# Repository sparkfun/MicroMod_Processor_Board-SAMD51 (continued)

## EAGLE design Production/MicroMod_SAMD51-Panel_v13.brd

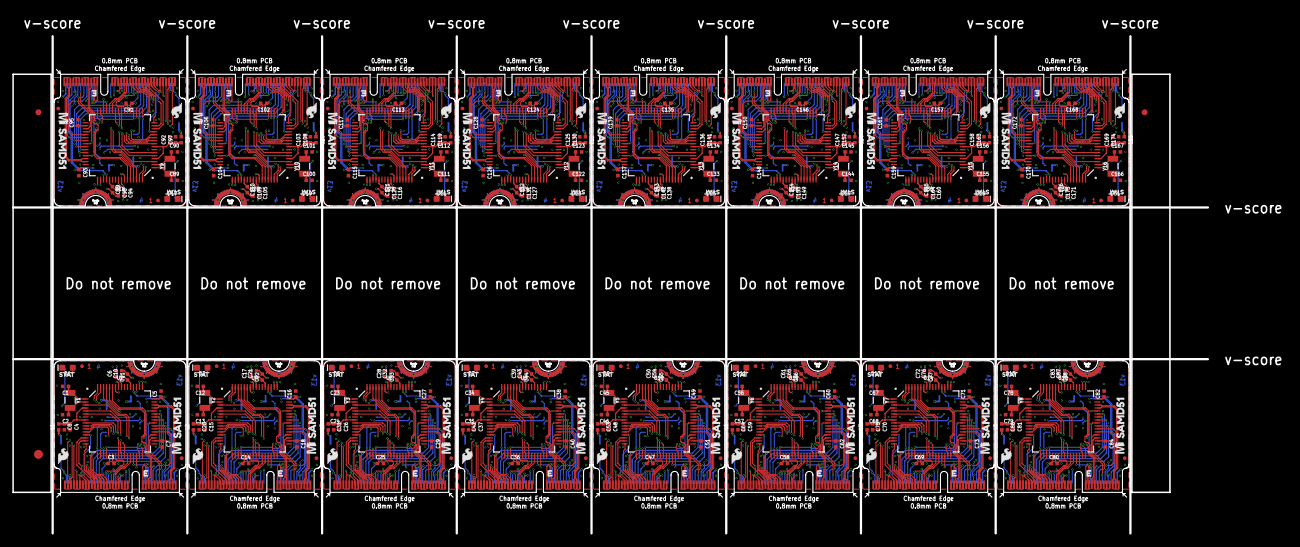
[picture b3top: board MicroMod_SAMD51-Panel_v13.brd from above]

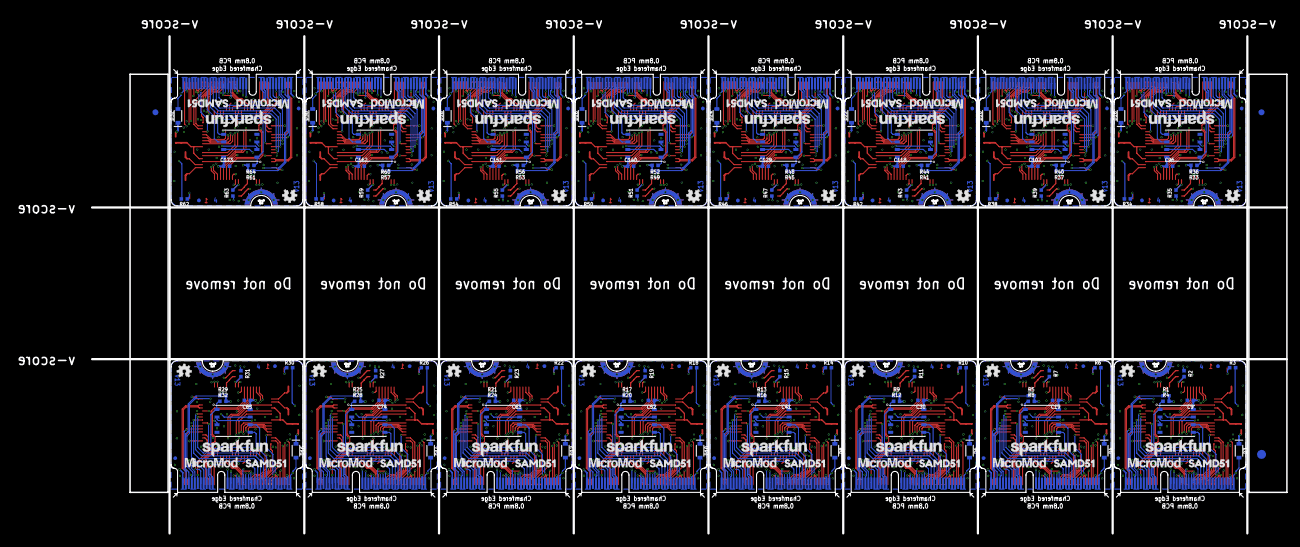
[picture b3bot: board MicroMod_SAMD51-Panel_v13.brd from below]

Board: 4 copper layers, 199.6 x 83.1 mm, 550 parts (211 on the bottom side), 912 nets.

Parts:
C1, C2, C12, C13, C23, C24, C34, C35, C45, C46, C56, C57, C67, C68, C78, C79, C89, C90, C100, C101, C111, C112, C122, C123, C133, C134, C144, C145, C155, C156, C166, C167: 15pF; 0402-TIGHT
C3, C5, C6, C7, C9, C10, C14, C16, C17, C18, C19, C21, C25, C27, C28, C29, C30, C32, C36, C38, C39, C40, C41, C43, C47, C49, C50, C51, C52, C54, C58, C60, C61, C62, C63, C65, C69, C71, C72, C73, C74, C76, C80, C82, C83, C84, C85, C87, C91, C93, C94, C95, C96, C98, C102, C104, C105, C106, C107, C109, C113, C115, C116, C117, C118, C120, C124, C126, C127, C128, C129, C131, C135, C137, C138, C139, C140, C142, C146, C148, C149, C150, C151, C153, C157, C159, C160, C161, C162, C164, C168, C170, C171, C172, C173, C175: 0.1uF; 0402-TIGHT
C4, C8, C15, C20, C26, C31, C37, C42, C48, C53, C59, C64, C70, C75, C81, C86, C92, C97, C103, C108, C114, C119, C125, C130, C136, C141, C147, C152, C158, C163, C169, C174: 10uF; 0402-TIGHT
C11, C22, C33, C44, C55, C66, C77, C88, C99, C110, C121, C132, C143, C154, C165, C176: 4.7uF; 0402-TIGHT
D1, D2, D5, D7, D9, D11, D13, D15, D17, D19, D21, D23, D25, D27, D29, D31: BLUE; LED-0603
D3, D4, D6, D8, D10, D12, D14, D16, D18, D20, D22, D24, D26, D28, D30, D32: 1A/23V/620mV; SOD-323
E$1, E$2, E$3, E$4: FIDUCIAL-1X2
E$5, E$6: FIDUCIAL-1.5X3
FD1, FD2, FD3, FD4, FD5, FD6, FD7, FD8, FD9, FD10, FD11, FD12, FD13, FD14, FD15, FD16, FD17, FD18, FD19, FD20, FD21, FD22, FD23, FD24, FD25, FD26, FD27, FD28, FD29, FD30, FD31, FD32, FD33, FD34, FD35, FD36, FD37, FD38, FD39, FD40, FD41, FD42, FD43, FD44, FD45, FD46, FD47, FD48, FD49, FD50, FD51, FD52, FD53, FD54, FD55, FD56, FD57, FD58, FD59, FD60, FD61, FD62, FD63, FD64: FIDUCIALUFIDUCIAL; FIDUCIAL-MICRO
J1, J2, J3, J4, J5, J6, J7, J8, J9, J10, J11, J12, J13, J14, J15, J16: MICROMOD-2222; M.2-CARD-E-22
L1, L2, L3, L4, L5, L6, L7, L8, L9, L10, L11, L12, L13, L14, L15, L16: 30Ω; 0402-TIGHT
LOGO1, LOGO2, LOGO4, LOGO7, LOGO9, LOGO11, LOGO13, LOGO15, LOGO17, LOGO19, LOGO21, LOGO23, LOGO25, LOGO27, LOGO29, LOGO31: OSHW-LOGOMINI; OSHW-LOGO-MINI
LOGO3, LOGO5, LOGO6, LOGO8, LOGO10, LOGO12, LOGO14, LOGO16, LOGO18, LOGO20, LOGO22, LOGO24, LOGO26, LOGO28, LOGO30, LOGO32: SFE_LOGO_NAME.1_INCH; SFE_LOGO_NAME_.1
R1, R5, R9, R13, R17, R21, R25, R29, R33, R37, R41, R45, R49, R53, R57, R61: 10k; 0402-TIGHT
R2, R3, R6, R7, R10, R11, R14, R15, R18, R19, R22, R23, R26, R27, R30, R31, R34, R35, R38, R39, R42, R43, R46, R47, R50, R51, R54, R55, R58, R59, R62, R63: 1k; 0402-TIGHT
R4, R8, R12, R16, R20, R24, R28, R32, R36, R40, R44, R48, R52, R56, R60, R64: 100k; 0402-TIGHT
U1, U3, U5, U7, U9, U11, U13, U15, U17, U19, U21, U23, U25, U27, U29, U31: W25QXX128MBIT-6X5-NO_CENTER; WSON-8-6X5-NO_CENTERPAD
U2, U4, U6, U8, U10, U12, U14, U16, U18, U20, U22, U24, U26, U28, U30, U32: ATSAMD51J20A-A; TQFP64
U$1, U$11, U$17, U$23, U$29, U$35, U$41, U$47, U$53, U$59, U$65, U$71, U$77, U$83, U$89, U$95: MICROMOD_MI_LOGO_.35
U$2, U$3, U$5, U$6, U$13, U$14, U$19, U$20, U$25, U$26, U$31, U$32, U$37, U$38, U$43, U$44, U$49, U$50, U$55, U$56, U$61, U$62, U$67, U$68, U$73, U$74, U$79, U$80, U$85, U$86, U$91, U$92: SAMD510
U$4, U$12, U$18, U$24, U$30, U$36, U$42, U$48, U$54, U$60, U$66, U$72, U$78, U$84, U$90, U$96: MICROMOD_LOGO_.35
U$7, U$9, U$15, U$21, U$27, U$33, U$39, U$45, U$51, U$57, U$63, U$69, U$75, U$81, U$87, U$93: SFE_LOGO_FLAME_.1
U$8, U$10, U$16, U$22, U$28, U$34, U$40, U$46, U$52, U$58, U$64, U$70, U$76, U$82, U$88, U$94: STAT0
Y1, Y2, Y3, Y4, Y5, Y6, Y7, Y8, Y9, Y10, Y11, Y12, Y13, Y14, Y15, Y16: 32.768kHz; CRYSTAL-SMD-3.2X1.5MM

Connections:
3.3V: C3.1, C5.1, C6.1, C7.1, C9.1, D3.C, J2.72, L1.1, R1.2, R2.2, R4.2, U1.8, U2.21, U2.34, U2.48, U2.56
3.3V1: C14.1, C16.1, C17.1, C18.1, C19.1, D4.C, J1.72, L2.1, R5.2, R7.2, R8.2, U3.8, U4.21, U4.34, U4.48, U4.56
3.3V2: C25.1, C27.1, C28.1, C29.1, C30.1, D6.C, J3.72, L3.1, R9.2, R11.2, R12.2, U5.8, U6.21, U6.34, U6.48, U6.56
3.3V3: C36.1, C38.1, C39.1, C40.1, C41.1, D8.C, J4.72, L4.1, R13.2, R15.2, R16.2, U7.8, U8.21, U8.34, U8.48, U8.56
3.3V4: C47.1, C49.1, C50.1, C51.1, C52.1, D10.C, J5.72, L5.1, R17.2, R19.2, R20.2, U9.8, U10.21, U10.34, U10.48, U10.56
3.3V5: C58.1, C60.1, C61.1, C62.1, C63.1, D12.C, J6.72, L6.1, R21.2, R23.2, R24.2, U11.8, U12.21, U12.34, U12.48, U12.56
3.3V6: C69.1, C71.1, C72.1, C73.1, C74.1, D14.C, J7.72, L7.1, R25.2, R27.2, R28.2, U13.8, U14.21, U14.34, U14.48, U14.56
3.3V7: C80.1, C82.1, C83.1, C84.1, C85.1, D16.C, J8.72, L8.1, R29.2, R31.2, R32.2, U15.8, U16.21, U16.34, U16.48, U16.56
3.3V8: C91.1, C93.1, C94.1, C95.1, C96.1, D18.C, J9.72, L9.1, R33.2, R35.2, R36.2, U17.8, U18.21, U18.34, U18.48, U18.56
3.3V9: C102.1, C104.1, C105.1, C106.1, C107.1, D20.C, J10.72, L10.1, R37.2, R39.2, R40.2, U19.8, U20.21, U20.34, U20.48, U20.56
3.3V10: C113.1, C115.1, C116.1, C117.1, C118.1, D22.C, J11.72, L11.1, R41.2, R43.2, R44.2, U21.8, U22.21, U22.34, U22.48, U22.56
3.3V11: C124.1, C126.1, C127.1, C128.1, C129.1, D24.C, J12.72, L12.1, R45.2, R47.2, R48.2, U23.8, U24.21, U24.34, U24.48, U24.56
3.3V12: C135.1, C137.1, C138.1, C139.1, C140.1, D26.C, J13.72, L13.1, R49.2, R51.2, R52.2, U25.8, U26.21, U26.34, U26.48, U26.56
3.3V13: C146.1, C148.1, C149.1, C150.1, C151.1, D28.C, J14.72, L14.1, R53.2, R55.2, R56.2, U27.8, U28.21, U28.34, U28.48, U28.56
3.3V14: C157.1, C159.1, C160.1, C161.1, C162.1, D30.C, J15.72, L15.1, R57.2, R59.2, R60.2, U29.8, U30.21, U30.34, U30.48, U30.56
3.3V15: C168.1, C170.1, C171.1, C172.1, C173.1, D32.C, J16.72, L16.1, R61.2, R63.2, R64.2, U31.8, U32.21, U32.34, U32.48, U32.56
3.3V_EN: J2.4, U2.38
3.3V_EN1: J1.4, U4.38
3.3V_EN2: J3.4, U6.38
3.3V_EN3: J4.4, U8.38
3.3V_EN4: J5.4, U10.38
3.3V_EN5: J6.4, U12.38
3.3V_EN6: J7.4, U14.38
3.3V_EN7: J8.4, U16.38
3.3V_EN8: J9.4, U18.38
3.3V_EN9: J10.4, U20.38
3.3V_EN10: J11.4, U22.38
3.3V_EN11: J12.4, U24.38
3.3V_EN12: J13.4, U26.38
3.3V_EN13: J14.4, U28.38
3.3V_EN14: J15.4, U30.38
3.3V_EN15: J16.4, U32.38
3.3V_IN: D3.A, J2.2, J2.74
3.3V_IN1: D4.A, J1.2, J1.74
3.3V_IN2: D6.A, J3.2, J3.74
3.3V_IN3: D8.A, J4.2, J4.74
3.3V_IN4: D10.A, J5.2, J5.74
3.3V_IN5: D12.A, J6.2, J6.74
3.3V_IN6: D14.A, J7.2, J7.74
3.3V_IN7: D16.A, J8.2, J8.74
3.3V_IN8: D18.A, J9.2, J9.74
3.3V_IN9: D20.A, J10.2, J10.74
3.3V_IN10: D22.A, J11.2, J11.74
3.3V_IN11: D24.A, J12.2, J12.74
3.3V_IN12: D26.A, J13.2, J13.74
3.3V_IN13: D28.A, J14.2, J14.74
3.3V_IN14: D30.A, J15.2, J15.74
3.3V_IN15: D32.A, J16.2, J16.74
!CS: J2.55, U2.16
!CS1: J1.55, U4.16
!CS1!: R4.1, U1.1, U2.20
!CS1!1: R8.1, U3.1, U4.20
!CS1!2: R12.1, U5.1, U6.20
!CS1!3: R16.1, U7.1, U8.20
!CS1!4: R20.1, U9.1, U10.20
!CS1!5: R24.1, U11.1, U12.20
!CS1!6: R28.1, U13.1, U14.20
!CS1!7: R32.1, U15.1, U16.20
!CS1!8: R36.1, U17.1, U18.20
!CS1!9: R40.1, U19.1, U20.20
!CS1!10: R44.1, U21.1, U22.20
!CS1!11: R48.1, U23.1, U24.20
!CS1!12: R52.1, U25.1, U26.20
!CS1!13: R56.1, U27.1, U28.20
!CS1!14: R60.1, U29.1, U30.20
!CS1!15: R64.1, U31.1, U32.20
!CS2: J3.55, U6.16
!CS3: J4.55, U8.16
!CS4: J5.55, U10.16
!CS5: J6.55, U12.16
!CS6: J7.55, U14.16
!CS7: J8.55, U16.16
!CS8: J9.55, U18.16
!CS9: J10.55, U20.16
!CS10: J11.55, U22.16
!CS11: J12.55, U24.16
!CS12: J13.55, U26.16
!CS13: J14.55, U28.16
!CS14: J15.55, U30.16
!CS15: J16.55, U32.16
!HOLD!: U1.7, U2.50
!HOLD!1: U3.7, U4.50
!HOLD!2: U5.7, U6.50
!HOLD!3: U7.7, U8.50
!HOLD!4: U9.7, U10.50
!HOLD!5: U11.7, U12.50
!HOLD!6: U13.7, U14.50
!HOLD!7: U15.7, U16.50
!HOLD!8: U17.7, U18.50
!HOLD!9: U19.7, U20.50
!HOLD!10: U21.7, U22.50
!HOLD!11: U23.7, U24.50
!HOLD!12: U25.7, U26.50
!HOLD!13: U27.7, U28.50
!HOLD!14: U29.7, U30.50
!HOLD!15: U31.7, U32.50
!RESET: J2.6, R1.1, U2.52
!RESET1: J1.6, R5.1, U4.52
!RESET2: J3.6, R9.1, U6.52
!RESET3: J4.6, R13.1, U8.52
!RESET4: J5.6, R17.1, U10.52
!RESET5: J6.6, R21.1, U12.52
!RESET6: J7.6, R25.1, U14.52
!RESET7: J8.6, R29.1, U16.52
!RESET8: J9.6, R33.1, U18.52
!RESET9: J10.6, R37.1, U20.52
!RESET10: J11.6, R41.1, U22.52
!RESET11: J12.6, R45.1, U24.52
!RESET12: J13.6, R49.1, U26.52
!RESET13: J14.6, R53.1, U28.52
!RESET14: J15.6, R57.1, U30.52
!RESET15: J16.6, R61.1, U32.52
!WP!: U1.3, U2.49
!WP!1: U3.3, U4.49
!WP!2: U5.3, U6.49
!WP!3: U7.3, U8.49
!WP!4: U9.3, U10.49
!WP!5: U11.3, U12.49
!WP!6: U13.3, U14.49
!WP!7: U15.3, U16.49
!WP!8: U17.3, U18.49
!WP!9: U19.3, U20.49
!WP!10: U21.3, U22.49
!WP!11: U23.3, U24.49
!WP!12: U25.3, U26.49
!WP!13: U27.3, U28.49
!WP!14: U29.3, U30.49
!WP!15: U31.3, U32.49
A0/DAC: J2.34, U2.3
A0/DAC1: J1.34, U4.3
A0/DAC2: J3.34, U6.3
A0/DAC3: J4.34, U8.3
A0/DAC4: J5.34, U10.3
A0/DAC5: J6.34, U12.3
A0/DAC6: J7.34, U14.3
A0/DAC7: J8.34, U16.3
A0/DAC8: J9.34, U18.3
A0/DAC9: J10.34, U20.3
A0/DAC10: J11.34, U22.3
A0/DAC11: J12.34, U24.3
A0/DAC12: J13.34, U26.3
A0/DAC13: J14.34, U28.3
A0/DAC14: J15.34, U30.3
A0/DAC15: J16.34, U32.3
A1: J2.38, U2.61
A2: J1.38, U4.61
A2/PWM0: J2.32, U2.62
A2/PWM1: J1.32, U4.62
A2/PWM2: J3.32, U6.62
A2/PWM3: J4.32, U8.62
A2/PWM4: J5.32, U10.62
A2/PWM5: J6.32, U12.62
A2/PWM6: J7.32, U14.62
A2/PWM7: J8.32, U16.62
A2/PWM8: J9.32, U18.62
A2/PWM9: J10.32, U20.62
A2/PWM10: J11.32, U22.62
A2/PWM11: J12.32, U24.62
A2/PWM12: J13.32, U26.62
A2/PWM13: J14.32, U28.62
A2/PWM14: J15.32, U30.62
A2/PWM15: J16.32, U32.62
A3: J1.49, U4.64
A3/PWM1: J2.47, U2.63
A3/PWM2: J1.47, U4.63
A3/PWM3: J3.47, U6.63
A3/PWM4: J4.47, U8.63
A3/PWM5: J5.47, U10.63
A3/PWM6: J6.47, U12.63
A3/PWM7: J7.47, U14.63
A3/PWM8: J8.47, U16.63
A3/PWM9: J9.47, U18.63
A3/PWM10: J10.47, U20.63
A3/PWM11: J11.47, U22.63
A3/PWM12: J12.47, U24.63
A3/PWM13: J13.47, U26.63
A3/PWM14: J14.47, U28.63
A3/PWM15: J15.47, U30.63
A3/PWM16: J16.47, U32.63
A4: J2.49, U2.64
A5: J3.38, U6.61
A6: J3.49, U6.64
A7: J4.38, U8.61
A8: J4.49, U8.64
A9: J5.38, U10.61
A10: J5.49, U10.64
A11: J6.38, U12.61
A12: J6.49, U12.64
A13: J7.38, U14.61
A14: J7.49, U14.64
A15: J8.38, U16.61
A16: J8.49, U16.64
A17: J9.38, U18.61
A18: J9.49, U18.64
A19: J10.38, U20.61
A20: J10.49, U20.64
A21: J11.38, U22.61
A22: J11.49, U22.64
A23: J12.38, U24.61
A24: J12.49, U24.64
A25: J13.38, U26.61
A26: J13.49, U26.64
A27: J14.38, U28.61
A28: J14.49, U28.64
A29: J15.38, U30.61
A30: J15.49, U30.64
A31: J16.38, U32.61
A32: J16.49, U32.64
CIPO: J2.61, U2.15
CIPO1: U1.2, U2.19
CIPO2: J1.61, U4.15
CIPO3: U3.2, U4.19
CIPO4: J3.61, U6.15
CIPO5: U5.2, U6.19
CIPO6: J4.61, U8.15
CIPO7: U7.2, U8.19
CIPO8: J5.61, U10.15
CIPO9: U9.2, U10.19
CIPO10: J6.61, U12.15
CIPO11: U11.2, U12.19
CIPO12: J7.61, U14.15
CIPO13: U13.2, U14.19
CIPO14: J8.61, U16.15
CIPO15: U15.2, U16.19
CIPO16: J9.61, U18.15
CIPO17: U17.2, U18.19
CIPO18: J10.61, U20.15
CIPO19: U19.2, U20.19
CIPO20: J11.61, U22.15
CIPO21: U21.2, U22.19
CIPO22: J12.61, U24.15
CIPO23: U23.2, U24.19
CIPO24: J13.61, U26.15
CIPO25: U25.2, U26.19
CIPO26: J14.61, U28.15
CIPO27: U27.2, U28.19
CIPO28: J15.61, U30.15
CIPO29: U29.2, U30.19
CIPO30: J16.61, U32.15
CIPO31: U31.2, U32.19
COPI: J2.59, U2.13
COPI1: U1.5, U2.18
COPI2: J1.59, U4.13
COPI3: U3.5, U4.18
COPI4: J3.59, U6.13
COPI5: U5.5, U6.18
COPI6: J4.59, U8.13
COPI7: U7.5, U8.18
COPI8: J5.59, U10.13
COPI9: U9.5, U10.18
COPI10: J6.59, U12.13
COPI11: U11.5, U12.18
COPI12: J7.59, U14.13
COPI13: U13.5, U14.18
COPI14: J8.59, U16.13
COPI15: U15.5, U16.18
COPI16: J9.59, U18.13
COPI17: U17.5, U18.18
COPI18: J10.59, U20.13
COPI19: U19.5, U20.18
COPI20: J11.59, U22.13
COPI21: U21.5, U22.18
COPI22: J12.59, U24.13
COPI23: U23.5, U24.18
COPI24: J13.59, U26.13
COPI25: U25.5, U26.18
COPI26: J14.59, U28.13
COPI27: U27.5, U28.18
COPI28: J15.59, U30.13
COPI29: U29.5, U30.18
COPI30: J16.59, U32.13
COPI31: U31.5, U32.18
D0: J2.10, U2.5
D1: J2.18, U2.6
D2: R6.2, U4.44
D2/G0: J2.40, U2.9
D2/G1: J1.40, U4.9
D2/G2: J3.40, U6.9
D2/G3: J4.40, U8.9
D2/G4: J5.40, U10.9
D2/G5: J6.40, U12.9
D2/G6: J7.40, U14.9
D2/G7: J8.40, U16.9
D2/G8: J9.40, U18.9
D2/G9: J10.40, U20.9
D2/G10: J11.40, U22.9
D2/G11: J12.40, U24.9
D2/G12: J13.40, U26.9
D2/G13: J14.40, U28.9
D2/G14: J15.40, U30.9
D2/G15: J16.40, U32.9
D3: J1.10, U4.5
D3/G1: J2.42, U2.10
D3/G2: J1.42, U4.10
D3/G3: J3.42, U6.10
D3/G4: J4.42, U8.10
D3/G5: J5.42, U10.10
D3/G6: J6.42, U12.10
D3/G7: J7.42, U14.10
D3/G8: J8.42, U16.10
D3/G9: J9.42, U18.10
D3/G10: J10.42, U20.10
D3/G11: J11.42, U22.10
D3/G12: J12.42, U24.10
D3/G13: J13.42, U26.10
D3/G14: J14.42, U28.10
D3/G15: J15.42, U30.10
D3/G16: J16.42, U32.10
D4: J1.18, U4.6
D4/G1: J1.44, U4.11
D4/G2: J2.44, U2.11
D4/G3: J3.44, U6.11
D4/G4: J4.44, U8.11
D4/G5: J5.44, U10.11
D4/G6: J6.44, U12.11
D4/G7: J7.44, U14.11
D4/G8: J8.44, U16.11
D4/G9: J9.44, U18.11
D4/G10: J10.44, U20.11
D4/G11: J11.44, U22.11
D4/G12: J12.44, U24.11
D4/G13: J13.44, U26.11
D4/G14: J14.44, U28.11
D4/G15: J15.44, U30.11
D4/G16: J16.44, U32.11
D5: J1.43, U4.27
D5/G1: J1.46, U4.12
D5/G2: J3.46, U6.12
D5/G3: J2.46, U2.12
D5/G4: J4.46, U8.12
D5/G5: J5.46, U10.12
D5/G6: J6.46, U12.12
D5/G7: J7.46, U14.12
D5/G8: J8.46, U16.12
D5/G9: J9.46, U18.12
D5/G10: J10.46, U20.12
D5/G11: J11.46, U22.12
D5/G12: J12.46, U24.12
D5/G13: J13.46, U26.12
D5/G14: J14.46, U28.12
D5/G15: J15.46, U30.12
D5/G16: J16.46, U32.12
D6: J1.41, U4.28
D6/G1: J1.48, U4.23
D6/G2: J3.48, U6.23
D6/G3: J4.48, U8.23
D6/G4: J2.48, U2.23
D6/G5: J5.48, U10.23
D6/G6: J6.48, U12.23
D6/G7: J7.48, U14.23
D6/G8: J8.48, U16.23
D6/G9: J9.48, U18.23
D6/G10: J10.48, U20.23
D6/G11: J11.48, U22.23
D6/G12: J12.48, U24.23
D6/G13: J13.48, U26.23
D6/G14: J14.48, U28.23
D6/G15: J15.48, U30.23
D6/G16: J16.48, U32.23
D7: J1.67, U4.31
D7/G1: J1.73, U4.24
D7/G2: J3.73, U6.24
D7/G3: J4.73, U8.24
D7/G4: J5.73, U10.24
D7/G5: J2.73, U2.24
D7/G6: J6.73, U12.24
D7/G7: J7.73, U14.24
D7/G8: J8.73, U16.24
D7/G9: J9.73, U18.24
D7/G10: J10.73, U20.24
D7/G11: J11.73, U22.24
D7/G12: J12.73, U24.24
D7/G13: J13.73, U26.24
D7/G14: J14.73, U28.24
D7/G15: J15.73, U30.24
D7/G16: J16.73, U32.24
D8: J1.65, U4.32
D8/G1: J1.71, U4.25
D8/G2: J3.71, U6.25
D8/G3: J4.71, U8.25
D8/G4: J5.71, U10.25
D8/G5: J6.71, U12.25
D8/G6: J2.71, U2.25
D8/G7: J7.71, U14.25
D8/G8: J8.71, U16.25
D8/G9: J9.71, U18.25
D8/G10: J10.71, U20.25
D8/G11: J11.71, U22.25
D8/G12: J12.71, U24.25
D8/G13: J13.71, U26.25
D8/G14: J14.71, U28.25
D8/G15: J15.71, U30.25
D8/G16: J16.71, U32.25
D9: R10.2, U6.44
D9/G1: J1.69, U4.26
D9/G2: J3.69, U6.26
D9/G3: J4.69, U8.26
D9/G4: J5.69, U10.26
D9/G5: J6.69, U12.26
D9/G6: J7.69, U14.26
D9/G7: J2.69, U2.26
D9/G8: J8.69, U16.26
D9/G9: J9.69, U18.26
D9/G10: J10.69, U20.26
D9/G11: J11.69, U22.26
D9/G12: J12.69, U24.26
D9/G13: J13.69, U26.26
D9/G14: J14.69, U28.26
D9/G15: J15.69, U30.26
D9/G16: J16.69, U32.26
D10: J2.67, U2.31
D11: J2.65, U2.32
D12: J3.10, U6.5
D13: R3.2, U2.44
D14: J3.18, U6.6
D15: J3.43, U6.27
D16: J3.41, U6.28
D17: J3.67, U6.31
D18: J3.65, U6.32
D19: R14.2, U8.44
D20: J4.10, U8.5
D21: J4.18, U8.6
D22: J4.43, U8.27
D23: J4.41, U8.28
D24: J4.67, U8.31
D25: J4.65, U8.32
D26: R18.2, U10.44
D27: J5.10, U10.5
D28: J5.18, U10.6
D29: J5.43, U10.27
D30: J5.41, U10.28
D31: J5.67, U10.31
D32: J5.65, U10.32
D33: R22.2, U12.44
D34: J6.10, U12.5
D35: J6.18, U12.6
D36: J6.43, U12.27
D37: J6.41, U12.28
D38: J2.43, U2.27
D39: J2.41, U2.28
D40: J6.67, U12.31
D41: J6.65, U12.32
D42: R26.2, U14.44
D43: J7.10, U14.5
D44: J7.18, U14.6
D45: J7.43, U14.27
D46: J7.41, U14.28
D47: J7.67, U14.31
D48: J7.65, U14.32
D49: R30.2, U16.44
D50: J8.10, U16.5
D51: J8.18, U16.6
D52: J8.43, U16.27
D53: J8.41, U16.28
D54: J8.67, U16.31
D55: J8.65, U16.32
D56: R34.2, U18.44
D57: J9.10, U18.5
D58: J9.18, U18.6
D59: J9.43, U18.27
D60: J9.41, U18.28
D61: J9.67, U18.31
D62: J9.65, U18.32
D63: R38.2, U20.44
D64: J10.10, U20.5
D65: J10.18, U20.6
D66: J10.43, U20.27
D67: J10.41, U20.28
D68: J10.67, U20.31
D69: J10.65, U20.32
D70: R42.2, U22.44
D71: J11.10, U22.5
D72: J11.18, U22.6
D73: J11.43, U22.27
D74: J11.41, U22.28
D75: J11.67, U22.31
D76: J11.65, U22.32
D77: R46.2, U24.44
D78: J12.10, U24.5
D79: J12.18, U24.6
D80: J12.43, U24.27
D81: J12.41, U24.28
D82: J12.67, U24.31
D83: J12.65, U24.32
D84: R50.2, U26.44
D85: J13.10, U26.5
D86: J13.18, U26.6
D87: J13.43, U26.27
D88: J13.41, U26.28
D89: J13.67, U26.31
D90: J13.65, U26.32
D91: R54.2, U28.44
D92: J14.10, U28.5
D93: J14.18, U28.6
D94: J14.43, U28.27
D95: J14.41, U28.28
D96: J14.67, U28.31
D97: J14.65, U28.32
D98: R58.2, U30.44
D99: J15.10, U30.5
D100: J15.18, U30.6
D101: J15.43, U30.27
D102: J15.41, U30.28
D103: J15.67, U30.31
D104: J15.65, U30.32
D105: R62.2, U32.44
D106: J16.10, U32.5
D107: J16.18, U32.6
D108: J16.43, U32.27
D109: J16.41, U32.28
D110: J16.67, U32.31
D111: J16.65, U32.32
D+/USBHOST_D+: J2.3, U2.46
D+/USBHOST_D+1: J1.3, U4.46
D+/USBHOST_D+2: J3.3, U6.46
D+/USBHOST_D+3: J4.3, U8.46
D+/USBHOST_D+4: J5.3, U10.46
D+/USBHOST_D+5: J6.3, U12.46
D+/USBHOST_D+6: J7.3, U14.46
D+/USBHOST_D+7: J8.3, U16.46
D+/USBHOST_D+8: J9.3, U18.46
D+/USBHOST_D+9: J10.3, U20.46
D+/USBHOST_D+10: J11.3, U22.46
D+/USBHOST_D+11: J12.3, U24.46
D+/USBHOST_D+12: J13.3, U26.46
D+/USBHOST_D+13: J14.3, U28.46
D+/USBHOST_D+14: J15.3, U30.46
D+/USBHOST_D+15: J16.3, U32.46
D-/USBHOST_D-: J2.5, U2.45
D-/USBHOST_D-1: J1.5, U4.45
D-/USBHOST_D-2: J3.5, U6.45
D-/USBHOST_D-3: J4.5, U8.45
D-/USBHOST_D-4: J5.5, U10.45
D-/USBHOST_D-5: J6.5, U12.45
D-/USBHOST_D-6: J7.5, U14.45
D-/USBHOST_D-7: J8.5, U16.45
D-/USBHOST_D-8: J9.5, U18.45
D-/USBHOST_D-9: J10.5, U20.45
D-/USBHOST_D-10: J11.5, U22.45
D-/USBHOST_D-11: J12.5, U24.45
D-/USBHOST_D-12: J13.5, U26.45
D-/USBHOST_D-13: J14.5, U28.45
D-/USBHOST_D-14: J15.5, U30.45
D-/USBHOST_D-15: J16.5, U32.45
GND: C1.2, C2.2, C3.2, C4.2, C5.2, C6.2, C7.2, C8.2, C9.2, C10.2, C11.2, D1.C, J2.1, J2.7, J2.33, J2.36, J2.39, J2.45, J2.75, J2.GND1, J2.GND2, J2.GND3, U1.4, U2.7, U2.22, U2.33, U2.47, U2.54
GND1: C12.2, C13.2, C14.2, C15.2, C16.2, C17.2, C18.2, C19.2, C20.2, C21.2, C22.2, D2.C, J1.1, J1.7, J1.33, J1.36, J1.39, J1.45, J1.75, J1.GND1, J1.GND2, J1.GND3, U3.4, U4.7, U4.22, U4.33, U4.47, U4.54
GND2: C23.2, C24.2, C25.2, C26.2, C27.2, C28.2, C29.2, C30.2, C31.2, C32.2, C33.2, D5.C, J3.1, J3.7, J3.33, J3.36, J3.39, J3.45, J3.75, J3.GND1, J3.GND2, J3.GND3, U5.4, U6.7, U6.22, U6.33, U6.47, U6.54
GND3: C34.2, C35.2, C36.2, C37.2, C38.2, C39.2, C40.2, C41.2, C42.2, C43.2, C44.2, D7.C, J4.1, J4.7, J4.33, J4.36, J4.39, J4.45, J4.75, J4.GND1, J4.GND2, J4.GND3, U7.4, U8.7, U8.22, U8.33, U8.47, U8.54
GND4: C45.2, C46.2, C47.2, C48.2, C49.2, C50.2, C51.2, C52.2, C53.2, C54.2, C55.2, D9.C, J5.1, J5.7, J5.33, J5.36, J5.39, J5.45, J5.75, J5.GND1, J5.GND2, J5.GND3, U9.4, U10.7, U10.22, U10.33, U10.47, U10.54
GND5: C56.2, C57.2, C58.2, C59.2, C60.2, C61.2, C62.2, C63.2, C64.2, C65.2, C66.2, D11.C, J6.1, J6.7, J6.33, J6.36, J6.39, J6.45, J6.75, J6.GND1, J6.GND2, J6.GND3, U11.4, U12.7, U12.22, U12.33, U12.47, U12.54
GND6: C67.2, C68.2, C69.2, C70.2, C71.2, C72.2, C73.2, C74.2, C75.2, C76.2, C77.2, D13.C, J7.1, J7.7, J7.33, J7.36, J7.39, J7.45, J7.75, J7.GND1, J7.GND2, J7.GND3, U13.4, U14.7, U14.22, U14.33, U14.47, U14.54
GND7: C78.2, C79.2, C80.2, C81.2, C82.2, C83.2, C84.2, C85.2, C86.2, C87.2, C88.2, D15.C, J8.1, J8.7, J8.33, J8.36, J8.39, J8.45, J8.75, J8.GND1, J8.GND2, J8.GND3, U15.4, U16.7, U16.22, U16.33, U16.47, U16.54
GND8: C89.2, C90.2, C91.2, C92.2, C93.2, C94.2, C95.2, C96.2, C97.2, C98.2, C99.2, D17.C, J9.1, J9.7, J9.33, J9.36, J9.39, J9.45, J9.75, J9.GND1, J9.GND2, J9.GND3, U17.4, U18.7, U18.22, U18.33, U18.47, U18.54
GND9: C100.2, C101.2, C102.2, C103.2, C104.2, C105.2, C106.2, C107.2, C108.2, C109.2, C110.2, D19.C, J10.1, J10.7, J10.33, J10.36, J10.39, J10.45, J10.75, J10.GND1, J10.GND2, J10.GND3, U19.4, U20.7, U20.22, U20.33, U20.47, U20.54
GND10: C111.2, C112.2, C113.2, C114.2, C115.2, C116.2, C117.2, C118.2, C119.2, C120.2, C121.2, D21.C, J11.1, J11.7, J11.33, J11.36, J11.39, J11.45, J11.75, J11.GND1, J11.GND2, J11.GND3, U21.4, U22.7, U22.22, U22.33, U22.47, U22.54
GND11: C122.2, C123.2, C124.2, C125.2, C126.2, C127.2, C128.2, C129.2, C130.2, C131.2, C132.2, D23.C, J12.1, J12.7, J12.33, J12.36, J12.39, J12.45, J12.75, J12.GND1, J12.GND2, J12.GND3, U23.4, U24.7, U24.22, U24.33, U24.47, U24.54
GND12: C133.2, C134.2, C135.2, C136.2, C137.2, C138.2, C139.2, C140.2, C141.2, C142.2, C143.2, D25.C, J13.1, J13.7, J13.33, J13.36, J13.39, J13.45, J13.75, J13.GND1, J13.GND2, J13.GND3, U25.4, U26.7, U26.22, U26.33, U26.47, U26.54
GND13: C144.2, C145.2, C146.2, C147.2, C148.2, C149.2, C150.2, C151.2, C152.2, C153.2, C154.2, D27.C, J14.1, J14.7, J14.33, J14.36, J14.39, J14.45, J14.75, J14.GND1, J14.GND2, J14.GND3, U27.4, U28.7, U28.22, U28.33, U28.47, U28.54
GND14: C155.2, C156.2, C157.2, C158.2, C159.2, C160.2, C161.2, C162.2, C163.2, C164.2, C165.2, D29.C, J15.1, J15.7, J15.33, J15.36, J15.39, J15.45, J15.75, J15.GND1, J15.GND2, J15.GND3, U29.4, U30.7, U30.22, U30.33, U30.47, U30.54
GND15: C166.2, C167.2, C168.2, C169.2, C170.2, C171.2, C172.2, C173.2, C174.2, C175.2, C176.2, D31.C, J16.1, J16.7, J16.33, J16.36, J16.39, J16.45, J16.75, J16.GND1, J16.GND2, J16.GND3, U31.4, U32.7, U32.22, U32.33, U32.47, U32.54
HOST_ENABLE: J2.8, U2.51
HOST_ENABLE1: J1.8, U4.51
HOST_ENABLE2: J3.8, U6.51
HOST_ENABLE3: J4.8, U8.51
HOST_ENABLE4: J5.8, U10.51
HOST_ENABLE5: J6.8, U12.51
HOST_ENABLE6: J7.8, U14.51
HOST_ENABLE7: J8.8, U16.51
HOST_ENABLE8: J9.8, U18.51
HOST_ENABLE9: J10.8, U20.51
HOST_ENABLE10: J11.8, U22.51
HOST_ENABLE11: J12.8, U24.51
HOST_ENABLE12: J13.8, U26.51
HOST_ENABLE13: J14.8, U28.51
HOST_ENABLE14: J15.8, U30.51
HOST_ENABLE15: J16.8, U32.51
I2C_!INT!: J2.16, U2.37
I2C_!INT!1: J1.16, U4.37
I2C_!INT!2: J3.16, U6.37
I2C_!INT!3: J4.16, U8.37
I2C_!INT!4: J5.16, U10.37
I2C_!INT!5: J6.16, U12.37
I2C_!INT!6: J7.16, U14.37
I2C_!INT!7: J8.16, U16.37
I2C_!INT!8: J9.16, U18.37
I2C_!INT!9: J10.16, U20.37
I2C_!INT!10: J11.16, U22.37
I2C_!INT!11: J12.16, U24.37
I2C_!INT!12: J13.16, U26.37
I2C_!INT!13: J14.16, U28.37
I2C_!INT!14: J15.16, U30.37
I2C_!INT!15: J16.16, U32.37
I2S_CLK: J2.50, U2.39
I2S_CLK1: J1.50, U4.39
I2S_CLK2: J3.50, U6.39
I2S_CLK3: J4.50, U8.39
I2S_CLK4: J5.50, U10.39
I2S_CLK5: J6.50, U12.39
I2S_CLK6: J7.50, U14.39
I2S_CLK7: J8.50, U16.39
I2S_CLK8: J9.50, U18.39
I2S_CLK9: J10.50, U20.39
I2S_CLK10: J11.50, U22.39
I2S_CLK11: J12.50, U24.39
I2S_CLK12: J13.50, U26.39
I2S_CLK13: J14.50, U28.39
I2S_CLK14: J15.50, U30.39
I2S_CLK15: J16.50, U32.39
I2S_FS: J2.52, U2.41
I2S_FS1: J1.52, U4.41
I2S_FS2: J3.52, U6.41
I2S_FS3: J4.52, U8.41
I2S_FS4: J5.52, U10.41
I2S_FS5: J6.52, U12.41
I2S_FS6: J7.52, U14.41
I2S_FS7: J8.52, U16.41
I2S_FS8: J9.52, U18.41
I2S_FS9: J10.52, U20.41
I2S_FS10: J11.52, U22.41
I2S_FS11: J12.52, U24.41
I2S_FS12: J13.52, U26.41
I2S_FS13: J14.52, U28.41
I2S_FS14: J15.52, U30.41
I2S_FS15: J16.52, U32.41
I2S_MCLK: J2.58, U2.40
I2S_MCLK1: J1.58, U4.40
I2S_MCLK2: J3.58, U6.40
I2S_MCLK3: J4.58, U8.40
I2S_MCLK4: J5.58, U10.40
I2S_MCLK5: J6.58, U12.40
I2S_MCLK6: J7.58, U14.40
I2S_MCLK7: J8.58, U16.40
I2S_MCLK8: J9.58, U18.40
I2S_MCLK9: J10.58, U20.40
I2S_MCLK10: J11.58, U22.40
I2S_MCLK11: J12.58, U24.40
I2S_MCLK12: J13.58, U26.40
I2S_MCLK13: J14.58, U28.40
I2S_MCLK14: J15.58, U30.40
I2S_MCLK15: J16.58, U32.40
I2S_SDI: J2.54, U2.43
I2S_SDI1: J1.54, U4.43
I2S_SDI2: J3.54, U6.43
I2S_SDI3: J4.54, U8.43
I2S_SDI4: J5.54, U10.43
I2S_SDI5: J6.54, U12.43
I2S_SDI6: J7.54, U14.43
I2S_SDI7: J8.54, U16.43
I2S_SDI8: J9.54, U18.43
I2S_SDI9: J10.54, U20.43
I2S_SDI10: J11.54, U22.43
I2S_SDI11: J12.54, U24.43
I2S_SDI12: J13.54, U26.43
I2S_SDI13: J14.54, U28.43
I2S_SDI14: J15.54, U30.43
I2S_SDI15: J16.54, U32.43
I2S_SDO: J2.56, U2.42
I2S_SDO1: J1.56, U4.42
I2S_SDO2: J3.56, U6.42
I2S_SDO3: J4.56, U8.42
I2S_SDO4: J5.56, U10.42
I2S_SDO5: J6.56, U12.42
I2S_SDO6: J7.56, U14.42
I2S_SDO7: J8.56, U16.42
I2S_SDO8: J9.56, U18.42
I2S_SDO9: J10.56, U20.42
I2S_SDO10: J11.56, U22.42
I2S_SDO11: J12.56, U24.42
I2S_SDO12: J13.56, U26.42
I2S_SDO13: J14.56, U28.42
I2S_SDO14: J15.56, U30.42
I2S_SDO15: J16.56, U32.42
unnamed: D1.A, R3.1
unnamed: D2.A, R6.1
unnamed: D5.A, R10.1
unnamed: D7.A, R14.1
unnamed: D9.A, R18.1
unnamed: D11.A, R22.1
unnamed: D13.A, R26.1
unnamed: D15.A, R30.1
unnamed: D17.A, R34.1
unnamed: D19.A, R38.1
unnamed: D21.A, R42.1
unnamed: D23.A, R46.1
unnamed: D25.A, R50.1
unnamed: D27.A, R54.1
unnamed: D29.A, R58.1
unnamed: D31.A, R62.1
RXI: J2.19, U2.59
RXI1: J1.19, U4.59
RXI2: J3.19, U6.59
RXI3: J4.19, U8.59
RXI4: J5.19, U10.59
RXI5: J6.19, U12.59
RXI6: J7.19, U14.59
RXI7: J8.19, U16.59
RXI8: J9.19, U18.59
RXI9: J10.19, U20.59
RXI10: J11.19, U22.59
RXI11: J12.19, U24.59
RXI12: J13.19, U26.59
RXI13: J14.19, U28.59
RXI14: J15.19, U30.59
RXI15: J16.19, U32.59
SCK: J2.57, U2.14
SCK1: U1.6, U2.17
SCK2: J1.57, U4.14
SCK3: U3.6, U4.17
SCK4: J3.57, U6.14
SCK5: U5.6, U6.17
SCK6: J4.57, U8.14
SCK7: U7.6, U8.17
SCK8: J5.57, U10.14
SCK9: U9.6, U10.17
SCK10: J6.57, U12.14
SCK11: U11.6, U12.17
SCK12: J7.57, U14.14
SCK13: U13.6, U14.17
SCK14: J8.57, U16.14
SCK15: U15.6, U16.17
SCK16: J9.57, U18.14
SCK17: U17.6, U18.17
SCK18: J10.57, U20.14
SCK19: U19.6, U20.17
SCK20: J11.57, U22.14
SCK21: U21.6, U22.17
SCK22: J12.57, U24.14
SCK23: U23.6, U24.17
SCK24: J13.57, U26.14
SCK25: U25.6, U26.17
SCK26: J14.57, U28.14
SCK27: U27.6, U28.17
SCK28: J15.57, U30.14
SCK29: U29.6, U30.17
SCK30: J16.57, U32.14
SCK31: U31.6, U32.17
SCL: J2.14, U2.35
SCL1: J1.14, U4.35
SCL1/TX1: J1.22, J1.53, U4.29
SCL1/TX2: J2.22, J2.53, U2.29
SCL1/TX3: J3.22, J3.53, U6.29
SCL1/TX4: J4.22, J4.53, U8.29
SCL1/TX5: J5.22, J5.53, U10.29
SCL1/TX6: J6.22, J6.53, U12.29
SCL1/TX7: J7.22, J7.53, U14.29
SCL1/TX8: J8.22, J8.53, U16.29
SCL1/TX9: J9.22, J9.53, U18.29
SCL1/TX10: J10.22, J10.53, U20.29
SCL1/TX11: J11.22, J11.53, U22.29
SCL1/TX12: J12.22, J12.53, U24.29
SCL1/TX13: J13.22, J13.53, U26.29
SCL1/TX14: J14.22, J14.53, U28.29
SCL1/TX15: J15.22, J15.53, U30.29
SCL1/TX16: J16.22, J16.53, U32.29
SCL2: J3.14, U6.35
SCL3: J4.14, U8.35
SCL4: J5.14, U10.35
SCL5: J6.14, U12.35
SCL6: J7.14, U14.35
SCL7: J8.14, U16.35
SCL8: J9.14, U18.35
SCL9: J10.14, U20.35
SCL10: J11.14, U22.35
SCL11: J12.14, U24.35
SCL12: J13.14, U26.35
SCL13: J14.14, U28.35
SCL14: J15.14, U30.35
SCL15: J16.14, U32.35
SDA: J2.12, U2.36
SDA1: J1.12, U4.36
SDA1/RX1: J1.20, J1.51, U4.30
SDA1/RX2: J2.20, J2.51, U2.30
SDA1/RX3: J3.20, J3.51, U6.30
SDA1/RX4: J4.20, J4.51, U8.30
SDA1/RX5: J5.20, J5.51, U10.30
SDA1/RX6: J6.20, J6.51, U12.30
SDA1/RX7: J7.20, J7.51, U14.30
SDA1/RX8: J8.20, J8.51, U16.30
SDA1/RX9: J9.20, J9.51, U18.30
SDA1/RX10: J10.20, J10.51, U20.30
SDA1/RX11: J11.20, J11.51, U22.30
SDA1/RX12: J12.20, J12.51, U24.30
SDA1/RX13: J13.20, J13.51, U26.30
SDA1/RX14: J14.20, J14.51, U28.30
SDA1/RX15: J15.20, J15.51, U30.30
SDA1/RX16: J16.20, J16.51, U32.30
SDA2: J3.12, U6.36
SDA3: J4.12, U8.36
SDA4: J5.12, U10.36
SDA5: J6.12, U12.36
SDA6: J7.12, U14.36
SDA7: J8.12, U16.36
SDA8: J9.12, U18.36
SDA9: J10.12, U20.36
SDA10: J11.12, U22.36
SDA11: J12.12, U24.36
SDA12: J13.12, U26.36
SDA13: J14.12, U28.36
SDA14: J15.12, U30.36
SDA15: J16.12, U32.36
SWDCK: J2.21, R2.1, U2.57
SWDCK1: J1.21, R7.1, U4.57
SWDCK2: J3.21, R11.1, U6.57
SWDCK3: J4.21, R15.1, U8.57
SWDCK4: J5.21, R19.1, U10.57
SWDCK5: J6.21, R23.1, U12.57
SWDCK6: J7.21, R27.1, U14.57
SWDCK7: J8.21, R31.1, U16.57
SWDCK8: J9.21, R35.1, U18.57
SWDCK9: J10.21, R39.1, U20.57
SWDCK10: J11.21, R43.1, U22.57
SWDCK11: J12.21, R47.1, U24.57
SWDCK12: J13.21, R51.1, U26.57
SWDCK13: J14.21, R55.1, U28.57
SWDCK14: J15.21, R59.1, U30.57
SWDCK15: J16.21, R63.1, U32.57
SWDIO: J2.23, U2.58
SWDIO1: J1.23, U4.58
SWDIO2: J3.23, U6.58
SWDIO3: J4.23, U8.58
SWDIO4: J5.23, U10.58
SWDIO5: J6.23, U12.58
SWDIO6: J7.23, U14.58
SWDIO7: J8.23, U16.58
SWDIO8: J9.23, U18.58
SWDIO9: J10.23, U20.58
SWDIO10: J11.23, U22.58
SWDIO11: J12.23, U24.58
SWDIO12: J13.23, U26.58
SWDIO13: J14.23, U28.58
SWDIO14: J15.23, U30.58
SWDIO15: J16.23, U32.58
TXO: J2.17, U2.60
TXO1: J1.17, U4.60
TXO2: J3.17, U6.60
TXO3: J4.17, U8.60
TXO4: J5.17, U10.60
TXO5: J6.17, U12.60
TXO6: J7.17, U14.60
TXO7: J8.17, U16.60
TXO8: J9.17, U18.60
TXO9: J10.17, U20.60
TXO10: J11.17, U22.60
TXO11: J12.17, U24.60
TXO12: J13.17, U26.60
TXO13: J14.17, U28.60
TXO14: J15.17, U30.60
TXO15: J16.17, U32.60
VCC: C10.1, C11.1, U2.53
VCC1: C21.1, C22.1, U4.53
VCC2: C32.1, C33.1, U6.53
VCC3: C43.1, C44.1, U8.53
VCC4: C54.1, C55.1, U10.53
VCC5: C65.1, C66.1, U12.53
VCC6: C76.1, C77.1, U14.53
VCC7: C87.1, C88.1, U16.53
VCC8: C98.1, C99.1, U18.53
VCC9: C109.1, C110.1, U20.53
VCC10: C120.1, C121.1, U22.53
VCC11: C131.1, C132.1, U24.53
VCC12: C142.1, C143.1, U26.53
VCC13: C153.1, C154.1, U28.53
VCC14: C164.1, C165.1, U30.53
VCC15: C175.1, C176.1, U32.53
VDDA: C4.1, C8.1, L1.2, U2.4, U2.8
VDDA1: C15.1, C20.1, L2.2, U4.4, U4.8
VDDA2: C26.1, C31.1, L3.2, U6.4, U6.8
VDDA3: C37.1, C42.1, L4.2, U8.4, U8.8
VDDA4: C48.1, C53.1, L5.2, U10.4, U10.8
VDDA5: C59.1, C64.1, L6.2, U12.4, U12.8
VDDA6: C70.1, C75.1, L7.2, U14.4, U14.8
VDDA7: C81.1, C86.1, L8.2, U16.4, U16.8
VDDA8: C92.1, C97.1, L9.2, U18.4, U18.8
VDDA9: C103.1, C108.1, L10.2, U20.4, U20.8
VDDA10: C114.1, C119.1, L11.2, U22.4, U22.8
VDDA11: C125.1, C130.1, L12.2, U24.4, U24.8
VDDA12: C136.1, C141.1, L13.2, U26.4, U26.8
VDDA13: C147.1, C152.1, L14.2, U28.4, U28.8
VDDA14: C158.1, C163.1, L15.2, U30.4, U30.8
VDDA15: C169.1, C174.1, L16.2, U32.4, U32.8
XIN1: C12.1, U4.1, Y2.P$1
XIN2: C23.1, U6.1, Y3.P$1
XIN3: C34.1, U8.1, Y4.P$1
XIN4: C45.1, U10.1, Y5.P$1
XIN5: C56.1, U12.1, Y6.P$1
XIN6: C67.1, U14.1, Y7.P$1
XIN7: C78.1, U16.1, Y8.P$1
XIN8: C89.1, U18.1, Y9.P$1
XIN9: C100.1, U20.1, Y10.P$1
XIN10: C111.1, U22.1, Y11.P$1
XIN11: C122.1, U24.1, Y12.P$1
XIN12: C133.1, U26.1, Y13.P$1
XIN13: C144.1, U28.1, Y14.P$1
XIN14: C155.1, U30.1, Y15.P$1
XIN15: C166.1, U32.1, Y16.P$1
XIN32: C1.1, U2.1, Y1.P$1
XOUT1: C13.1, U4.2, Y2.P$2
XOUT2: C24.1, U6.2, Y3.P$2
XOUT3: C35.1, U8.2, Y4.P$2
XOUT4: C46.1, U10.2, Y5.P$2
XOUT5: C57.1, U12.2, Y6.P$2
XOUT6: C68.1, U14.2, Y7.P$2
XOUT7: C79.1, U16.2, Y8.P$2
XOUT8: C90.1, U18.2, Y9.P$2
XOUT9: C101.1, U20.2, Y10.P$2
XOUT10: C112.1, U22.2, Y11.P$2
XOUT11: C123.1, U24.2, Y12.P$2
XOUT12: C134.1, U26.2, Y13.P$2
XOUT13: C145.1, U28.2, Y14.P$2
XOUT14: C156.1, U30.2, Y15.P$2
XOUT15: C167.1, U32.2, Y16.P$2
XOUT32: C2.1, U2.2, Y1.P$2

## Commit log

2020-04-21 Renames files
2020-04-21 Adds notes for quad spi, spi, and analog pins to schematic
2020-04-22 Adds decoupling caps, adds I2S, and moves analog and digital pins
2020-04-29 Fixes schematic - adds second i2c, adds additional digital pins, and adds PWM pins
2020-04-30 Puts i2c on correct pin
2020-04-30 Renumbers pins
2020-04-30 Adds A3 to SAMD51, adds PWM to A2 and A3 net names
2020-04-30 Corrects isolate on polygons, adds two other ground pours, and one power pour
2020-05-05 Trace routing for QSPI, and other SPI busses
2020-05-05 Updates Micro mod connector to latest version
2020-05-06 More trace routing
2020-05-07 Adds much better trace routing - rips up other routing
2020-05-07 Finishes trace routing
2020-05-07 Touch up on ground pour
2020-05-08 Cleans up trace routing
2020-05-08 Adds silk, cleans up schematic
2020-05-09 Removes reset button
2020-05-11 Updates processor board with new screw design
2020-05-12 Updates symobl for SAMD51 to latest
2020-05-19 Updates Design
2020-05-19 Changes Ferrite bead to 0402, completes trace work since symbol for SAMD51 was recreated
    * Changes all parts to 0402 tight and fixes traces accordingly
2020-05-20 Adds Differential ADC lines, battery voltage connection, 3.3V enable line
    * Also adds diode to prevent backpowering 3.3V line from RTC_3V
2020-05-20 Adds gerbers of design
2020-05-21 Adds MicroMod logos
2020-05-21 Adds new gerbers to account for new silk
2020-05-21 Movers gerbers to production file
2020-05-21 Adds a testing carrier board so that I can test the functionality of the samd51
2020-05-21 Finishes trace work on Test board - needs some silk
2020-05-22 Adds silk to Testbed and moves SWD header
2020-05-22 Updates silk on testing carrier board
2020-05-22 Fixes very minor DRC errors
2020-05-27 Updates testing carrier board with all nets added and half of teh new ones added
2020-05-27 Finishes routing board
2020-05-27 Adds labels to testing carrier board
2020-06-16 Initial commit of board files
2020-06-23 Adds basic analog and digital pins
2020-06-25 Modifies about half of the variant.cpp file for
2020-07-21 Fills pin definitions in variants, fixes I2S and D13 which were swapped (I2S Bus was crossing IOSETs)
2020-07-21 Adds pin numbering to variants.h, fixes comments in variants.cpp
2020-07-30 Moves arduino files to a different folder, adds processor board to boards.txt
2020-08-05 Updates the CPP and .H file
    * Unfortunately it looks like I didn't do a symoblic link correctly and so I had to overwrite what was already in the repo. Mostly the small issues like incorrect pin numbering have been fixed.
2020-08-07 Changes so that SPI and I2C work
2020-08-13 Various testing elements in Variant files regarding Serial1 and Serial2
    * Changes old SPI naming convention to new one
    * Moves some pins around for more thought out layout (more details to come)
2020-08-13 changes prepended text so correctly identify the micromod addition
2020-08-13 Begins routing, removes old
2020-08-17 Adds routing to all but a few lines
2020-08-17 Finishing routing, and fixes minor DRC errors regarding wire stubs
2020-08-17 Updates SparkFun silk, rolls version to v11, fixes some traces that were not crossing others at 90 degrees.
2020-08-20 Moves cap at top of board, adjusts USB differential pair
2020-08-21 Increases dimension line width, fixes some proportional text, relabels A0 to includ DAC
    * Adds dimension measurements to measures layer
2020-08-21 Adds voltage range to schematic
2020-08-21 Panelization
2020-08-24 Updates the variant boards to reflect the final SAMD51 hardware
    * QSPI was removed in place of a secondary SPI port
    * The digital pins were rearranged to allow for full bus transers
    * Analog pins were also consolidated
    * Testing on overlapping serial2 and I2C1 were removed
    * Text was cleaned up and arranged to look dapper or pretty depending on how you feel about it
2020-08-26 Adds uf2 bootloader files
2020-08-26 Updates PINA0 starting at position 17
2020-09-02 Adds built binaries for uf2 bootloader
2020-09-22 Updates bootloader
2020-09-22 Correct mclk mask in bootloader
2020-09-22 Removes "built" folder
2020-09-22 Another try - changes ID_CORE and ID_SLOW in board_config.h
2020-09-22 Updates the micromodd connector and swaps the SPI pins
2020-09-22 Changes BOOT_USART_MASK to APADMASK in place of APBAMASK
2020-09-22 Fixes LED pin in bootloader
2020-09-22 updates bootloader once again
2020-09-22 Adds uf2 bootlader config files
2020-09-22 Fixes LED assignment in variant, routes SPI lines, rolls version to v12
2020-09-23 Fixes SERCOM for Serial1
2020-09-23 bootloader using different GCLK settings
2020-09-23 Removes extra .uf2 files, puts config files into their own folder,
    * Small fixes to variant files - analog pin defines, sercom djustments, and WIRE+SPI counts
2020-09-23 v12 panel
2020-09-23 fixes stray via
2020-09-23 v12 panel, take 2
2020-09-23 ENIG note added to special instructions
2020-10-02 Updates SPI clock names to correct abbreviation
2020-10-02 Updates name of the processor in the Arduino IDE by modifying the relevant variant files
    * Also adds uf2 bootloader path to the boards.txt file and the bootloader files
    in the relevant bootloader folder
2020-10-13 Fixes variant assignment name
2020-10-21 Fixes typo in usbhost_D+ net
2020-10-28 Updates CAN net names - CAN is not supported on SAM-"D" versions of the IC
2020-10-28 removes CAN the description of the pins in the variant files
2020-11-04 Removes buzzard labels, test sketches, old carrier board, and adds preprocessors for General purpose pins
2020-11-04 Adds keywords for general purpose pins
2020-11-06 Adds PWM pins, BATT_VIN, an chip select pins as pins that may be called directly
2020-11-09 Adds a few more #defines for more shared micromod pins
2021-09-14 Fixes swapped nets COPI/CIPO at flash chip
2021-09-15 Updates to latest parts
2021-09-15 Adds a few more vias, centers labels in schematic
2021-09-16 Panel update
2021-12-16 Adds new panel
    * To generate this panel I simply deleted everything but the board file, then I appended v13 to the name.
    * I then used the CAMMER ulp to remake the gerbers.
